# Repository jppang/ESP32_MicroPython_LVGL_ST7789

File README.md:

# ESP32_MicroPython_LVGL_ST7789
Try to build an ESP32 MicroPython firmware with LVGL and ST7789 drivers inside.

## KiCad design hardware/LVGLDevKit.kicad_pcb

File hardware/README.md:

This development kit for experimenting MicroPython and LVGL on ESP32 platform is designed by KiCad 6.

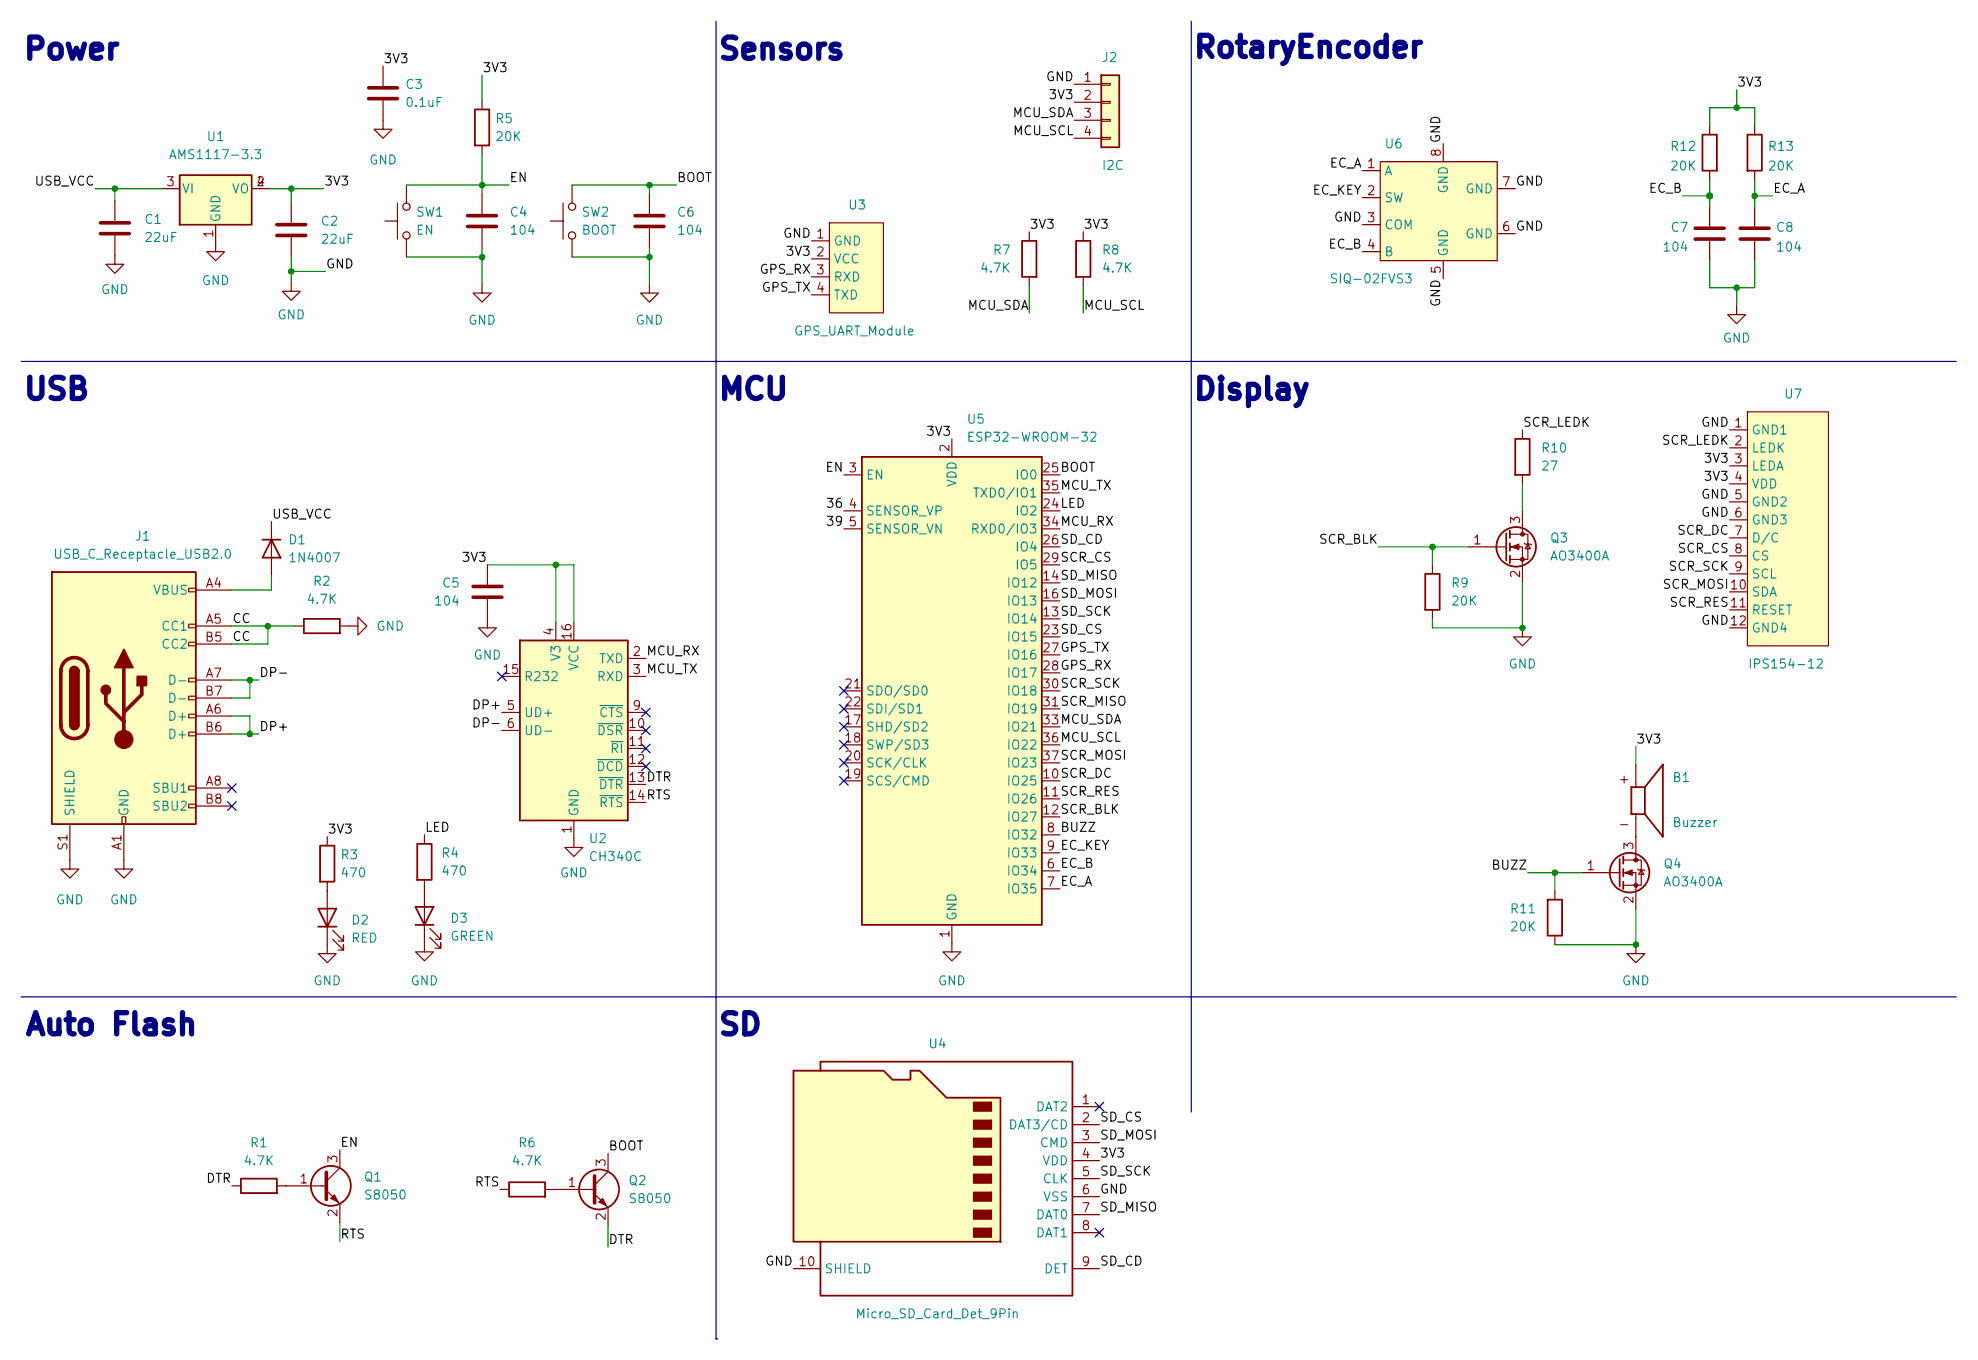
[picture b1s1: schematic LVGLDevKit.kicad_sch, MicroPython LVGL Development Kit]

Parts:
B1: Buzzer; Buzzer_CMT-0502-75-SMT-TR; PARTREV 1.0
C1, C2: 22uF; C_0805_2012Metric_Pad1.18x1.45mm_HandSolder
C3: 0.1uF; C_0805_2012Metric_Pad1.18x1.45mm_HandSolder
C4, C5, C6, C7, C8: 104; C_0805_2012Metric_Pad1.18x1.45mm_HandSolder
D1: 1N4007; D_SOD-323_HandSoldering
D2: RED; LED_0805_2012Metric_Pad1.15x1.40mm_HandSolder
D3: GREEN; LED_0805_2012Metric_Pad1.15x1.40mm_HandSolder
J1: USB_C_Receptacle_USB2.0; USB_C_Tabobao_16_Pin
J2: I2C; JST_PH_B4B-PH-K_1x04_P2.00mm_Vertical
Q1, Q2: S8050; SOT-23_Handsoldering
Q3: AO3400A; SOT-23_Handsoldering
Q4: AO3400A; SOT-23
R1, R2, R6, R7, R8: 4.7K; R_0805_2012Metric_Pad1.20x1.40mm_HandSolder
R3, R4: 470; R_0805_2012Metric_Pad1.20x1.40mm_HandSolder
R5, R9, R11, R12, R13: 20K; R_0805_2012Metric_Pad1.20x1.40mm_HandSolder
R10: 27; R_0805_2012Metric_Pad1.20x1.40mm_HandSolder
SW1: EN; SW_Push_SPST_NO_Alps_SKRK
SW2: BOOT; SW_Push_SPST_NO_Alps_SKRK
U1: AMS1117-3.3; SOT-223
U2: CH340C; SOP-16_3.9x9.9mm_P1.27mm
U3: GPS_UART_Module; JST_PH_B4B-PH-K_1x04_P2.00mm_Vertical
U4: Micro_SD_Card_Det_9Pin; microSD_Taobao_9_Pin_CD
U5: ESP32-WROOM-32
U6: SIQ-02FVS3; RotaryEncoder_Mitsumi_SIQ02FVS3
U7: IPS154-12; ZJYIPS154_PG04

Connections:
/3V3: B1.P, C2.1, C3.1, C5.1, J2.2, R3.1, R5.1, R7.1, R8.1, R12.1, R13.1, U1.2 (VO), U1.4 (VO), U2.4 (V3), U2.16 (VCC), U3.2 (VCC), U4.4 (VDD), U5.2 (VDD), U7.3 (LEDA), U7.4 (VDD)
/36: U5.4 (SENSOR_VP)
/39: U5.5 (SENSOR_VN)
/BOOT: C6.1, Q2.3 (C), SW2.2, U5.25 (IO0)
/BUZZ: Q4.1 (G), R11.2, U5.8 (IO32)
/CC: J1.A5 (CC1), J1.B5 (CC2), R2.1
/DP+: J1.A6 (D+), J1.B6 (D+), U2.5 (UD+)
/DP-: J1.A7 (D-), J1.B7 (D-), U2.6 (UD-)
/DTR: Q2.2 (E), R1.1, U2.13 (~DTR)
/EC_A: C8.1, R13.2, U5.7 (IO35), U6.1 (A)
/EC_B: C7.1, R12.2, U5.6 (IO34), U6.4 (B)
/EC_KEY: U5.9 (IO33), U6.2 (SW)
/EN: C4.1, Q1.3 (C), R5.2, SW1.2, U5.3 (EN)
/GPS_RX: U3.3 (RXD), U5.28 (IO17)
/GPS_TX: U3.4 (TXD), U5.27 (IO16)
/LED: R4.1, U5.24 (IO2)
/MCU_RX: U2.2 (TXD), U5.34 (RXD0/IO3)
/MCU_SCL: J2.4, R8.2, U5.36 (IO22)
/MCU_SDA: J2.3, R7.2, U5.33 (IO21)
/MCU_TX: U2.3 (RXD), U5.35 (TXD0/IO1)
/RTS: Q1.2 (E), R6.1, U2.14 (~RTS)
/SCR_BLK: Q3.1 (G), R9.1, U5.12 (IO27)
/SCR_CS: U5.29 (IO5), U7.8 (CS)
/SCR_DC: U5.10 (IO25), U7.7 (D/C)
/SCR_LEDK: R10.1, U7.2 (LEDK)
/SCR_MISO: U5.31 (IO19)
/SCR_MOSI: U5.37 (IO23), U7.10 (SDA)
/SCR_RES: U5.11 (IO26), U7.11 (RESET)
/SCR_SCK: U5.30 (IO18), U7.9 (SCL)
/SD_CD: U4.9 (DET), U5.26 (IO4)
/SD_CS: U4.2 (DAT3/CD), U5.23 (IO15)
/SD_MISO: U4.7 (DAT0), U5.14 (IO12)
/SD_MOSI: U4.3 (CMD), U5.16 (IO13)
/SD_SCK: U4.5 (CLK), U5.13 (IO14)
/USB_VCC: C1.1, D1.1 (K), U1.3 (VI)
GND: C1.2, C2.2, C3.2, C4.2, C5.2, C6.2, C7.2, C8.2, D2.1 (K), D3.1 (K), J1.A1 (GND), J1.A12 (GND), J1.B1 (GND), J1.B12 (GND), J1.S1 (SHIELD), J2.1, Q3.2 (S), Q4.2 (S), R2.2, R9.2, R11.1, SW1.1, SW2.1, U1.1 (GND), U2.1 (GND), U3.1 (GND), U4.6 (VSS), U4.10 (SHIELD), U5.1 (GND), U5.15 (GND), U5.38 (GND), U5.39 (GND), U6.3 (COM), U6.5 (GND), U6.6 (GND), U6.7 (GND), U6.8 (GND), U7.1 (GND1), U7.5 (GND2), U7.6 (GND3), U7.12 (GND4)
unnamed: B1.N, Q4.3 (D)
unnamed: D1.2 (A), J1.A4 (VBUS), J1.A9 (VBUS), J1.B4 (VBUS), J1.B9 (VBUS)
unnamed: D2.2 (A), R3.2
unnamed: D3.2 (A), R4.2
unnamed: Q1.1 (B), R1.2
unnamed: Q2.1 (B), R6.2
unnamed: Q3.3 (D), R10.2

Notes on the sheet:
RotaryEncoder
USB
Display
MCU
Power
Auto Flash
Sensors

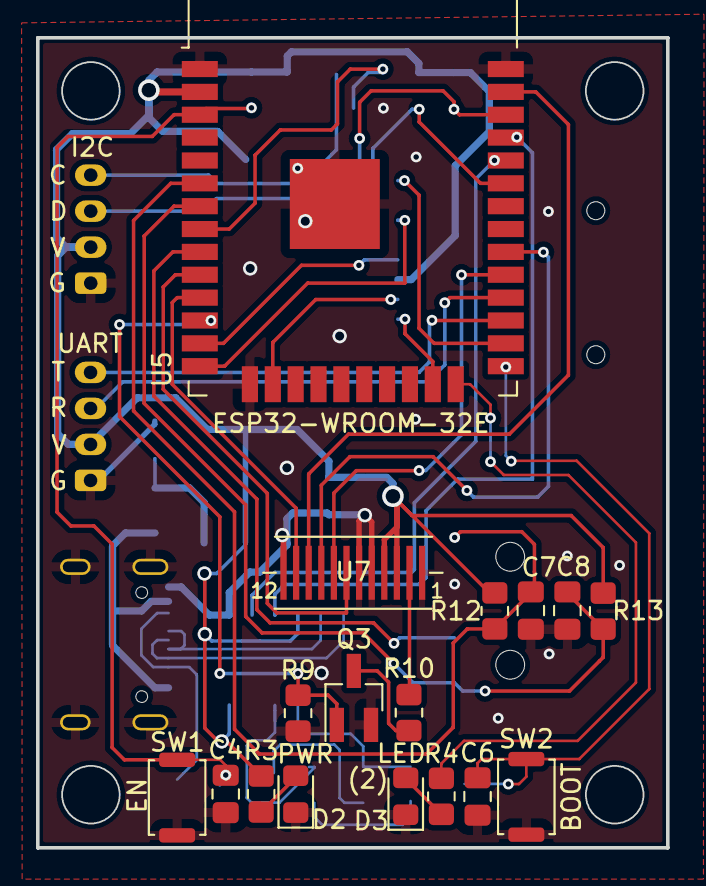
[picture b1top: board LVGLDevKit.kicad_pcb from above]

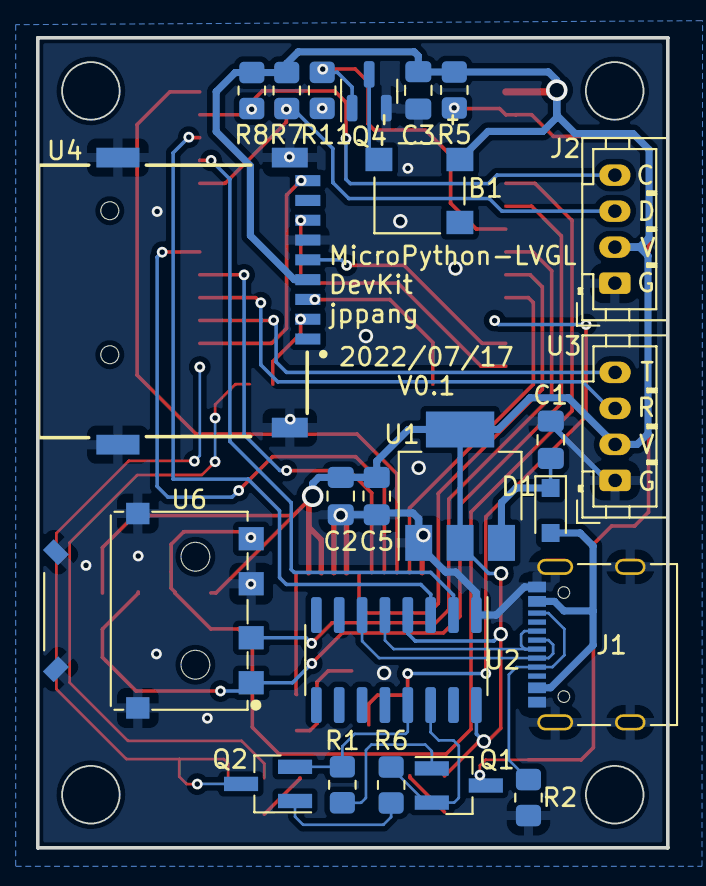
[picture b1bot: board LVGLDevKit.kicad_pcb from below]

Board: 2 copper layers, 35.0 x 45.0 mm, 40 parts (23 on the bottom side), 40 nets.
